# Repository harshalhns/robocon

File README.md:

# robocon
<pre>This project contains hardware details and AVR code for manual robot that was used in Robocon 2019. 
It is based on swerve drive. Four Atmega32 controllers are responsible for turning of each wheel to a precise target angle. 
These 4 slave controllers receive commands from master Atmega2560 via SPI. 
The robot is operated using Android mobile phone. It connects to phone through ESP8266 wifi module.</pre>

Movement of MR1: https://drive.google.com/file/d/1RZcdZKO_QcPA8YeLSfsehZz7-IaqJbko/view?ts=5e0452a6<br/>
Passing mech: https://drive.google.com/file/d/1aKHcwnHMSf9a8_czkzGeTRfraIhykFKB/view?ts=5e0452bf<br/>
Throwing mech: https://drive.google.com/file/d/1u2j3kQulj4zu3Mqgoj5k-V91Kau0ibW5/view?ts=5e045611<br/>
Movement of MR2: https://drive.google.com/file/d/1vg7AJLM3L7O4et1_eYZHAmFJQMHMDMgw/view?ts=5e045298<br/>

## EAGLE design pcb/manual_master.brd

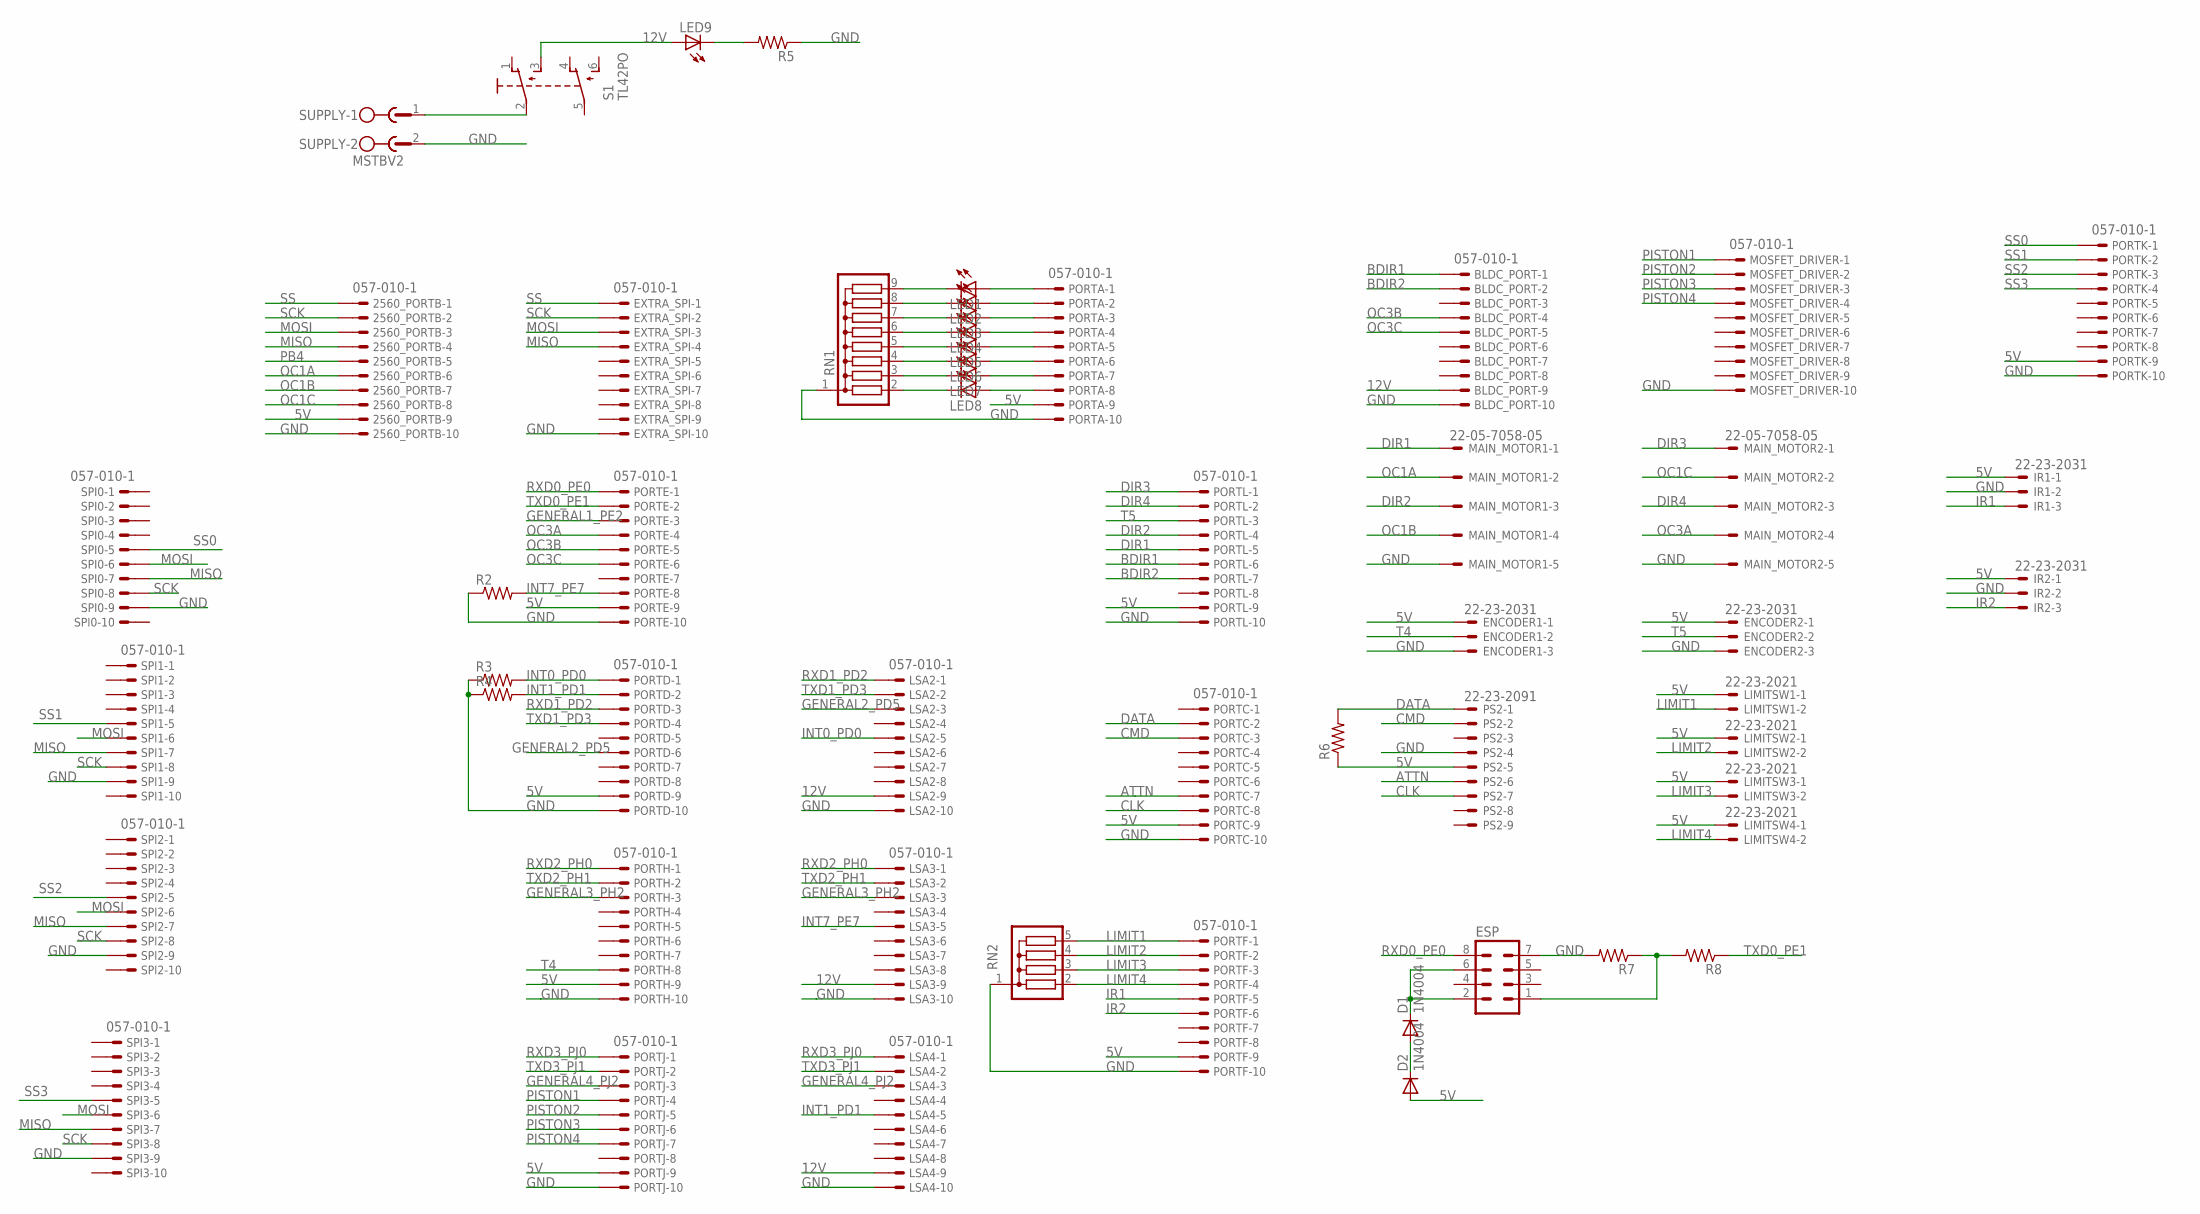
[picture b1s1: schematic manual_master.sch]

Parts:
2560_PORTB: 057-010-1
BLDC_PORT: 057-010-1
D1, D2: 1N4004; DO41-10
ENCODER1, ENCODER2: 22-23-2031
ESP: MA04-2
EXTRA_SPI: 057-010-1
IR1, IR2: 22-23-2031
LED1, LED2, LED3, LED4, LED5, LED6, LED7, LED8: LED3MM
LED9: LED5MM
LIMITSW1, LIMITSW2, LIMITSW3, LIMITSW4: 22-23-2021
LSA2, LSA3, LSA4: 057-010-1
MAIN_MOTOR1, MAIN_MOTOR2: 22-05-7058-05; 7395-05
MOSFET_DRIVER: 057-010-1
PORTA: 057-010-1
PORTC: 057-010-1
PORTD: 057-010-1
PORTE: 057-010-1
PORTF: 057-010-1
PORTH: 057-010-1
PORTJ: 057-010-1
PORTK: 057-010-1
PORTL: 057-010-1
PS2: 22-23-2091
R2, R3, R4, R5, R6, R7, R8: R-US_0207/10; 0207/10
RN1: G08R; SIL9
RN2: G04R; SIL5
S1: TL42PO; TL4XPO
SPI0, SPI1, SPI2, SPI3: 057-010-1
SUPPLY: MSTBV2

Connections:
5V: 2560_PORTB.9, D2.A, ENCODER1.1, ENCODER2.1, IR1.1, IR2.1, LIMITSW1.1, LIMITSW2.1, LIMITSW3.1, LIMITSW4.1, PORTA.9, PORTC.9, PORTD.9, PORTE.9, PORTF.9, PORTH.9, PORTJ.9, PORTK.9, PORTL.9, PS2.5, R6.1
12V: BLDC_PORT.9, LED9.A, LSA2.9, LSA3.9, LSA4.9, S1.3 (S)
ATTN: PORTC.7, PS2.6
BDIR1: BLDC_PORT.1, PORTL.6
BDIR2: BLDC_PORT.2, PORTL.7
CLK: PORTC.8, PS2.7
CMD: PORTC.3, PS2.2
DATA: PORTC.2, PS2.1, R6.2
DIR1: MAIN_MOTOR1.1, PORTL.5
DIR2: MAIN_MOTOR1.3, PORTL.4
DIR3: MAIN_MOTOR2.1, PORTL.1
DIR4: MAIN_MOTOR2.3, PORTL.2
GENERAL1_PE2: PORTE.3
GENERAL2_PD5: LSA2.3, PORTD.6
GENERAL3_PH2: LSA3.3, PORTH.3
GENERAL4_PJ2: LSA4.3, PORTJ.3
GND: 2560_PORTB.10, BLDC_PORT.10, ENCODER1.3, ENCODER2.3, ESP.7, EXTRA_SPI.10, IR1.2, IR2.2, LSA2.10, LSA3.10, LSA4.10, MAIN_MOTOR1.5, MAIN_MOTOR2.5, MOSFET_DRIVER.10, PORTA.10, PORTC.10, PORTD.10, PORTE.10, PORTF.10, PORTH.10, PORTJ.10, PORTK.10, PORTL.10, PS2.4, R2.1, R3.1, R4.1, R5.1, R7.2, RN1.1, RN2.1, SPI0.9, SPI1.9, SPI2.9, SPI3.9, SUPPLY.2
INT0_PD0: LSA2.5, PORTD.1, R3.2
INT1_PD1: LSA4.5, PORTD.2, R4.2
INT7_PE7: LSA3.5, PORTE.8, R2.2
IR1: IR1.3, PORTF.5
IR2: IR2.3, PORTF.6
LIMIT1: LIMITSW1.2, PORTF.1, RN2.5
LIMIT2: LIMITSW2.2, PORTF.2, RN2.4
LIMIT3: LIMITSW3.2, PORTF.3, RN2.3
LIMIT4: LIMITSW4.2, PORTF.4, RN2.2
MISO: 2560_PORTB.4, EXTRA_SPI.4, SPI0.7, SPI1.7, SPI2.7, SPI3.7
MOSI: 2560_PORTB.3, EXTRA_SPI.3, SPI0.6, SPI1.6, SPI2.6, SPI3.6
unnamed: D1.A, D2.C
unnamed: D1.C, ESP.2, ESP.6
unnamed: S1.2, SUPPLY.1
unnamed: LED9.K (C), R5.2
unnamed: LED1.A, PORTA.1
unnamed: LED2.A, PORTA.2
unnamed: LED3.A, PORTA.3
unnamed: LED4.A, PORTA.4
unnamed: LED5.A, PORTA.5
unnamed: LED6.A, PORTA.6
unnamed: LED7.A, PORTA.7
unnamed: LED8.A, PORTA.8
unnamed: LED1.K (C), RN1.9
unnamed: LED2.K (C), RN1.8
unnamed: ESP.1, R7.1, R8.2
unnamed: LED3.K (C), RN1.7
unnamed: LED4.K (C), RN1.6
unnamed: LED5.K (C), RN1.5
unnamed: LED6.K (C), RN1.4
unnamed: LED7.K (C), RN1.3
unnamed: LED8.K (C), RN1.2
OC1A: 2560_PORTB.6, MAIN_MOTOR1.2
OC1B: 2560_PORTB.7, MAIN_MOTOR1.4
OC1C: 2560_PORTB.8, MAIN_MOTOR2.2
OC3A: MAIN_MOTOR2.4, PORTE.4
OC3B: BLDC_PORT.4, PORTE.5
OC3C: BLDC_PORT.5, PORTE.6
PB4: 2560_PORTB.5
PISTON1: MOSFET_DRIVER.1, PORTJ.4
PISTON2: MOSFET_DRIVER.2, PORTJ.5
PISTON3: MOSFET_DRIVER.3, PORTJ.6
PISTON4: MOSFET_DRIVER.4, PORTJ.7
RXD0_PE0: ESP.8, PORTE.1
RXD1_PD2: LSA2.1, PORTD.3
RXD2_PH0: LSA3.1, PORTH.1
RXD3_PJ0: LSA4.1, PORTJ.1
SCK: 2560_PORTB.2, EXTRA_SPI.2, SPI0.8, SPI1.8, SPI2.8, SPI3.8
SS: 2560_PORTB.1, EXTRA_SPI.1
SS0: PORTK.1, SPI0.5
SS1: PORTK.2, SPI1.5
SS2: PORTK.3, SPI2.5
SS3: PORTK.4, SPI3.5
T4: ENCODER1.2, PORTH.8
T5: ENCODER2.2, PORTL.3
TXD0_PE1: PORTE.2, R8.1
TXD1_PD3: LSA2.2, PORTD.4
TXD2_PH1: LSA3.2, PORTH.2
TXD3_PJ1: LSA4.2, PORTJ.2

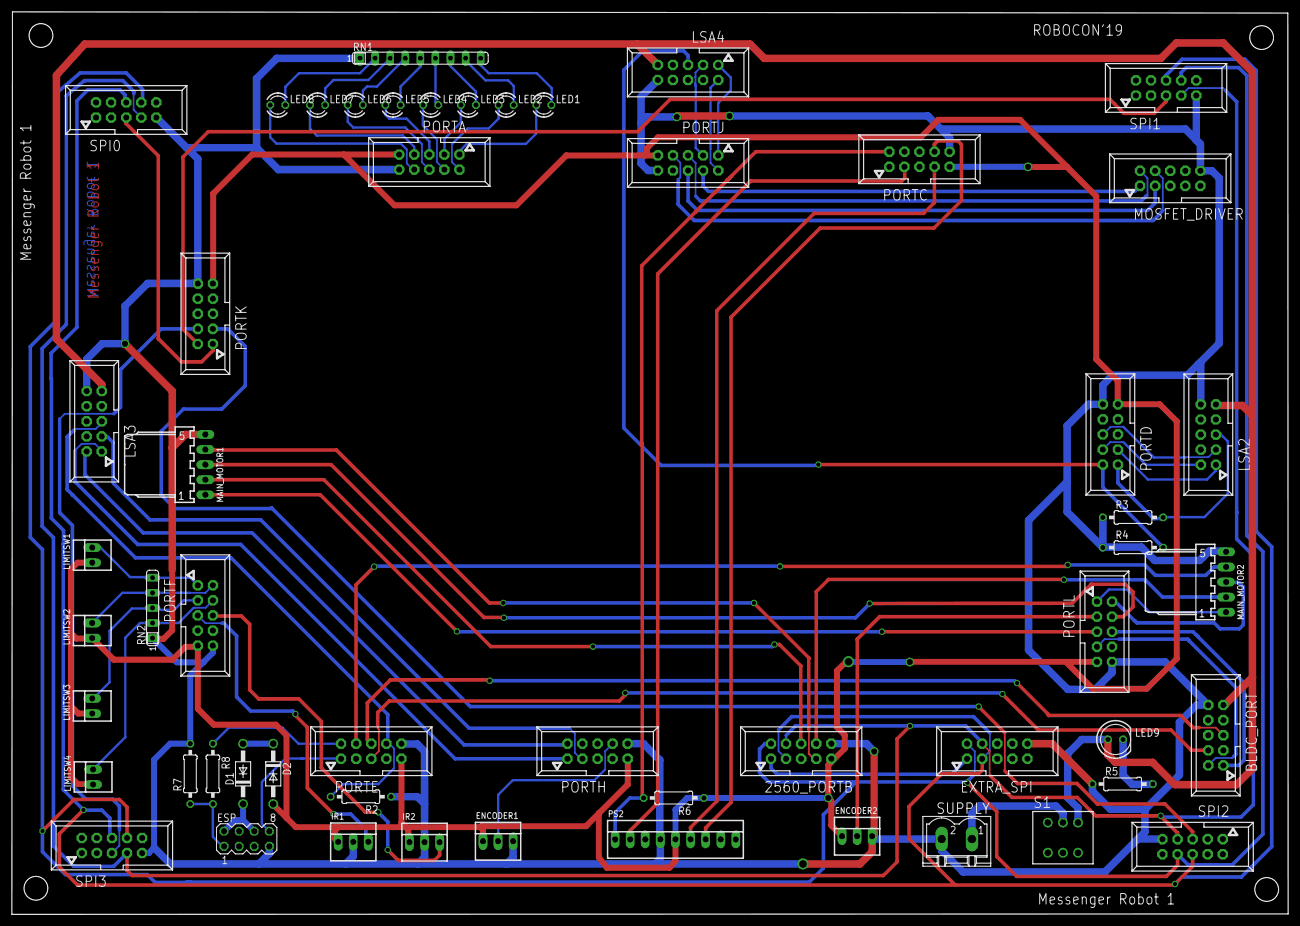
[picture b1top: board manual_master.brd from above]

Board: 2 copper layers, 214.9 x 152.0 mm, 54 parts (0 on the bottom side), 74 nets.

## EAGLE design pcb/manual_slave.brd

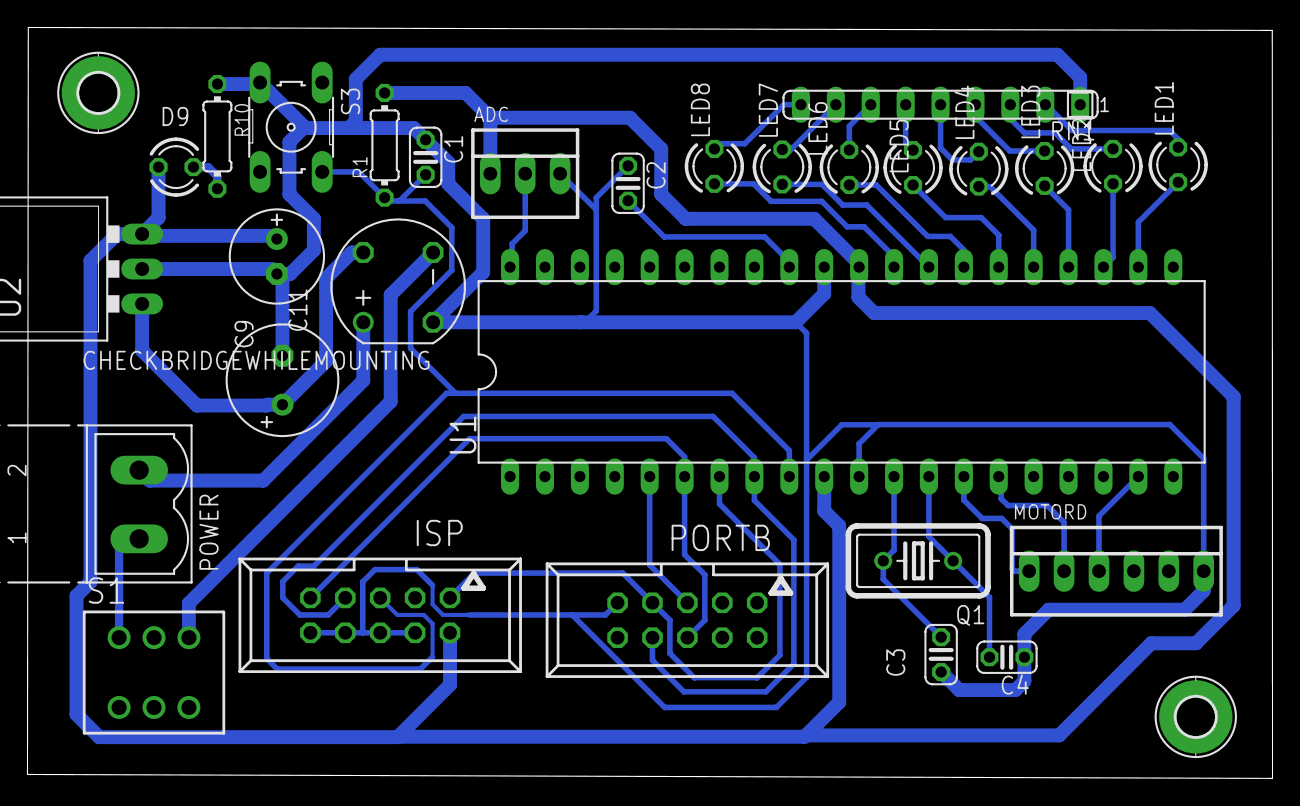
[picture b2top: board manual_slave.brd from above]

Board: 2 copper layers, 90.6 x 54.6 mm, 31 parts (0 on the bottom side), 35 nets.

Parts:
ADC: 22-23-2031
C1, C2: 0.1 uf; C025-024X044
C3, C4: 22uf; C025-024X044
C9: 470uf; E3,5-8
C11: 100uf; E2,5-7
CHECKBRIDGEWHILEMOUNTING: RB1A
D9: LED3MM
H3, H4: MOUNT-PAD-ROUND2.8; 2,8-PAD
ISP: 057-010-1
LED1, LED2, LED3, LED4, LED5, LED6, LED7, LED8: LED3MM
MOTORD: 22-23-2061
PORTB: 057-010-1
POWER: MSTBV2
Q1: HC18U-V
R1, R10: 0204/7
RN1: SIL9
S1: TL42PO; TL4XPO
S3: B3F-10XX
U1: ATmega 32; DIL40
U2: 7805; 78XXL

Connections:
ADC0: ADC.2, U1.40
GND: ADC.3, C1.1, C2.1, C3.1, C4.1, C9.-, C11.-, CHECKBRIDGEWHILEMOUNTING.AC2, ISP.4, ISP.6, ISP.8, ISP.10, MOTORD.6, PORTB.9, R10.1, RN1.1, S3.3, U1.11, U1.31, U2.GND
INT0: MOTORD.1, U1.14
INT1: MOTORD.2, U1.15
unnamed: CHECKBRIDGEWHILEMOUNTING.-, S1.3
unnamed: C3.2, Q1.2, U1.12
unnamed: C4.2, Q1.1, U1.13
unnamed: C2.2, U1.32
unnamed: D9.K, R10.2
unnamed: CHECKBRIDGEWHILEMOUNTING.+, POWER.2
unnamed: LED1.K, RN1.2
unnamed: LED2.K, RN1.3
unnamed: LED3.K, RN1.4
unnamed: LED4.K, RN1.5
unnamed: LED5.K, RN1.6
unnamed: LED6.K, RN1.7
unnamed: LED7.K, RN1.8
unnamed: LED8.K, RN1.9
unnamed: POWER.1, S1.1
unnamed: C9.+, CHECKBRIDGEWHILEMOUNTING.AC1, U2.IN
PB4: PORTB.5, U1.5
PB5: ISP.9, PORTB.6, U1.6
PB6: ISP.1, PORTB.7, U1.7
PB7: ISP.7, PORTB.8, U1.8
PC0: LED1.A, U1.22
PC1: LED2.A, U1.23
PC2: LED3.A, U1.24
PC3: LED4.A, U1.25
PC4: LED5.A, U1.26
PC5: LED6.A, U1.27
PC6: LED7.A, U1.28
PC7: LED8.A, U1.29
PWM: MOTORD.3, U1.19
RESET: C1.2, ISP.5, R1.1, S3.2, U1.9
VCC: ADC.1, C11.+, D9.A, ISP.2, R1.2, U1.10, U1.30, U2.OUT

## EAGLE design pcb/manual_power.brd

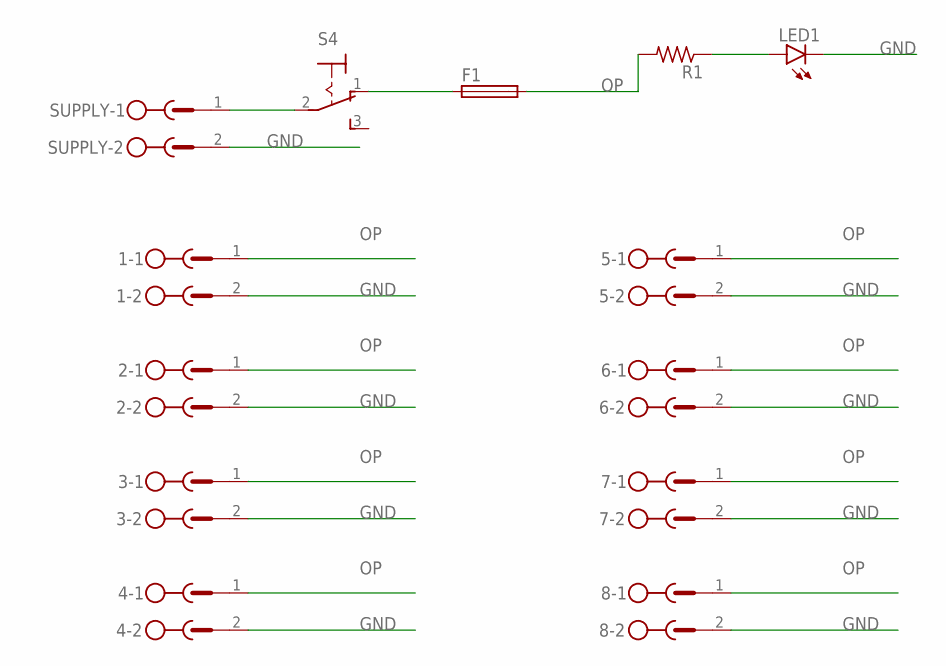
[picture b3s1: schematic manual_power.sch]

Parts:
1, 2, 3, 4, 5, 6, 7, 8: MSTBV2
F1: SH22
LED1: LED5MM
R1: R-US_0207/10; 0207/10
S4: 320-916
SUPPLY: MSTBV2

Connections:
GND: 1.2, 2.2, 3.2, 4.2, 5.2, 6.2, 7.2, 8.2, LED1.K (C), SUPPLY.2
unnamed: S4.2, SUPPLY.1
unnamed: LED1.A, R1.1
unnamed: F1.1, S4.1 (O)
OP: 1.1, 2.1, 3.1, 4.1, 5.1, 6.1, 7.1, 8.1, F1.2, R1.2

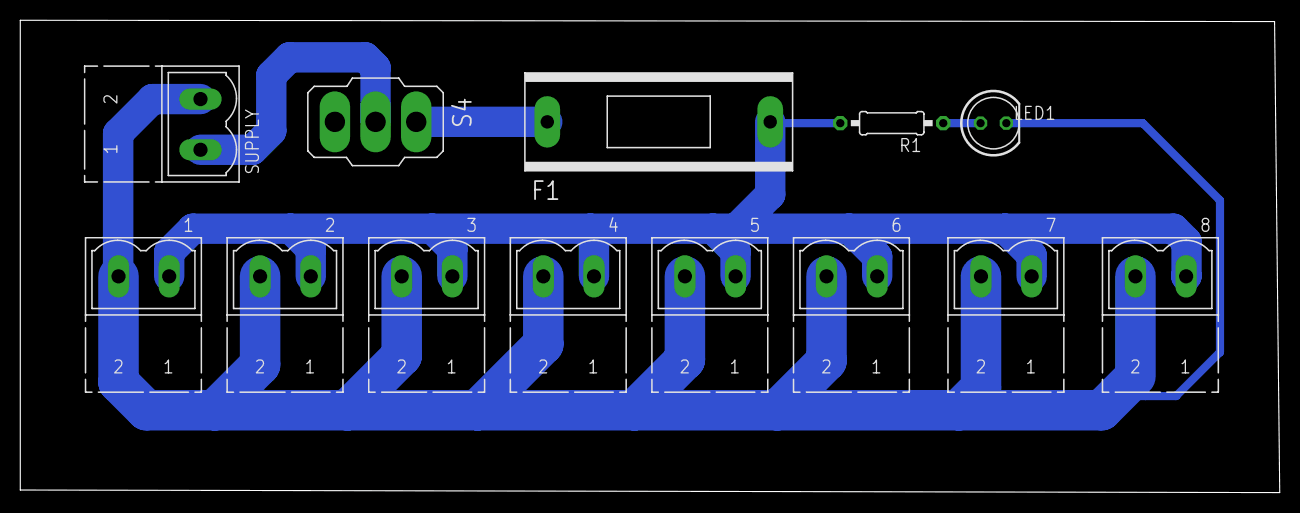
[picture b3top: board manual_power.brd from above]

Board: 2 copper layers, 124.3 x 46.6 mm, 13 parts (0 on the bottom side), 5 nets.

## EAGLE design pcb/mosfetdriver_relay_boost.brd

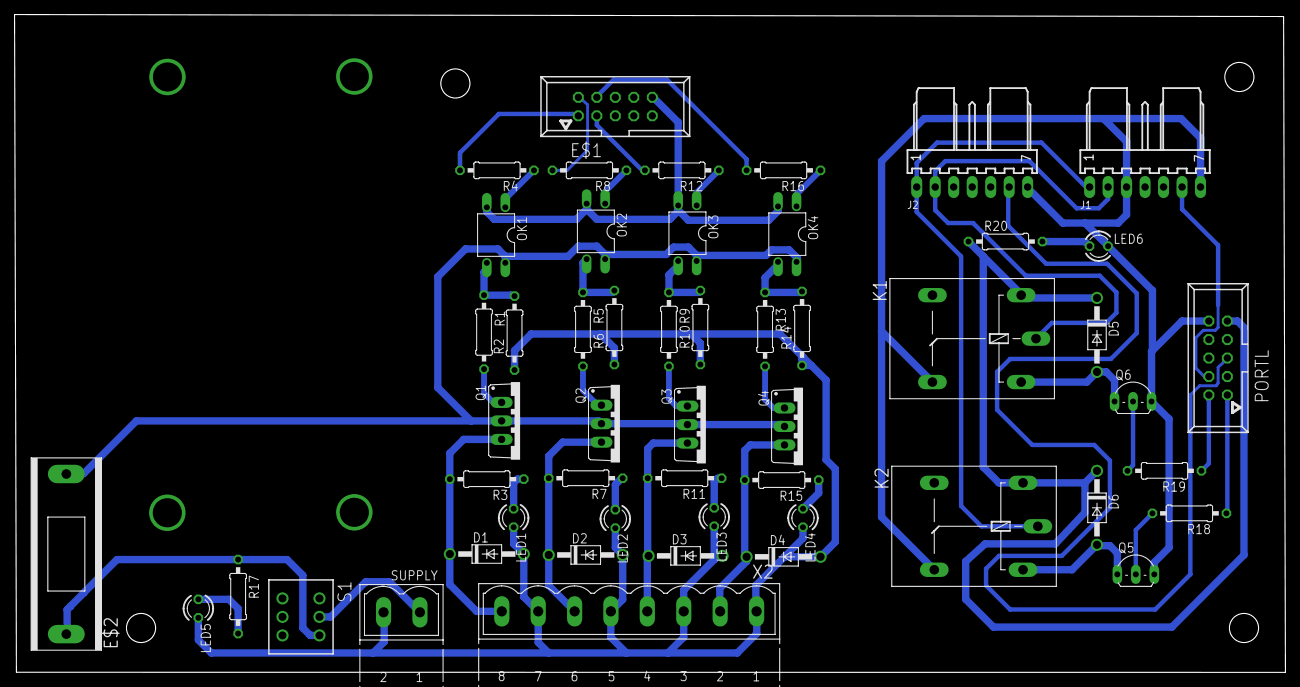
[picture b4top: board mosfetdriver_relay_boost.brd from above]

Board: 2 copper layers, 174.6 x 90.4 mm, 52 parts (0 on the bottom side), 38 nets.

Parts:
D1, D2, D3, D4, D5, D6: 1N4004; DO41-10
E$1: 057-010-1
E$2: SH22
J1, J2: 22-05-7078-07; 7395-07
K1, K2: G5L; G5LE
LED1, LED2, LED3, LED4, LED5, LED6: LED3MM
OK1, OK2, OK3, OK4: PC817; DIL04
PORTL: 057-010-1
Q1, Q2, Q3, Q4: IRF540; TO220BV
Q5, Q6: BC548; TO92-EBC
R1, R5, R9, R13: 100; 0207/10
R2, R6, R10, R14: 10k; 0207/10
R3, R7, R11, R15: 1k; 0207/10
R4, R8, R12, R16: 220; 0207/10
R17, R18, R19, R20: 0207/10
S1: TL46PO; TL4XPO
SUPPLY: MSTBV2
X2: MSTBV8

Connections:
12V: D5.C, D6.C, K1.1, K2.1, PORTL.9, R20.1
+12V: OK1.4, OK2.4, OK3.4, OK4.4, Q1.D, Q2.D, Q3.D, Q4.D, R17.1, S1.3
BRK: J1.1, J2.1, K2.P
EN: J1.2, J2.2, K1.P
GND: D1.A, D2.A, D3.A, D4.A, LED1.K, LED2.K, LED3.K, LED4.K, LED5.K, R2.1, R6.1, R10.1, R14.1, SUPPLY.2, X2.1, X2.3, X2.5, X2.7
GND1: OK1.2, OK2.2, OK3.2, OK4.2
GND2: J1.3, J1.7, J2.7, K1.O, K2.O, LED6.K, PORTL.10, Q5.E, Q6.E
unnamed: OK3.1, R12.1
unnamed: OK1.3, R1.1, R2.2
unnamed: Q1.G, R1.2
unnamed: LED1.A, R3.1
unnamed: OK4.1, R16.1
unnamed: OK2.3, R5.1, R6.2
unnamed: Q2.G, R5.2
unnamed: Q6.B, R19.2
unnamed: LED2.A, R7.1
unnamed: OK2.1, R8.1
unnamed: OK3.3, R9.1, R10.2
unnamed: Q3.G, R9.2
unnamed: Q5.B, R18.2
unnamed: LED3.A, R11.1
unnamed: OK1.1, R4.1
unnamed: OK4.3, R13.1, R14.2
unnamed: Q4.G, R13.2
unnamed: D5.A, K1.2, Q6.C
unnamed: LED4.A, R15.1
unnamed: S1.2, SUPPLY.1
unnamed: D6.A, K2.2, Q5.C
unnamed: LED5.A, R17.2
unnamed: LED6.A, R20.2
OP1: D1.C, Q1.S, R3.2, X2.8
OP2: D2.C, Q2.S, R7.2, X2.6
OP3: D3.C, Q3.S, R11.2, X2.4
OP4: D4.C, Q4.S, R15.2, X2.2
P0: PORTL.1, R18.1
P1: PORTL.2, R19.1
PWM1: J1.6, PORTL.4
PWM3: J2.6, PORTL.5

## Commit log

2019-07-27 Create manual_bot_slave
2019-07-27 Create manual_bot_master
2019-07-27 Create abc
2019-08-16 Update manual_bot_master
